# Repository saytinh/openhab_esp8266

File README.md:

# openhab_esp8266
Playground in smart home with openhab and esp8266. This one is built based on:

1. Openhab software (http://www.openhab.org/),  is a software for integrating different home automation systems and technologies into one single solution that allows over-arching automation rules and that offers uniform user interfaces.
2. Mosquitto (http://mosquitto.org/), is an open source (BSD licensed) message broker that implements the MQ Telemetry Transport protocol (MQTT protocol)
3. Adafruit MQTT Library (https://github.com/adafruit/Adafruit_MQTT_Library), is Arduino library used as a MQTT client on esp8266_program
4. Arduino-Temperature-Control-Library (https://github.com/milesburton/Arduino-Temperature-Control-Library), is Arduino Library used for DS18B20 temp sensor on esp8266_program

Thanks all above !!!

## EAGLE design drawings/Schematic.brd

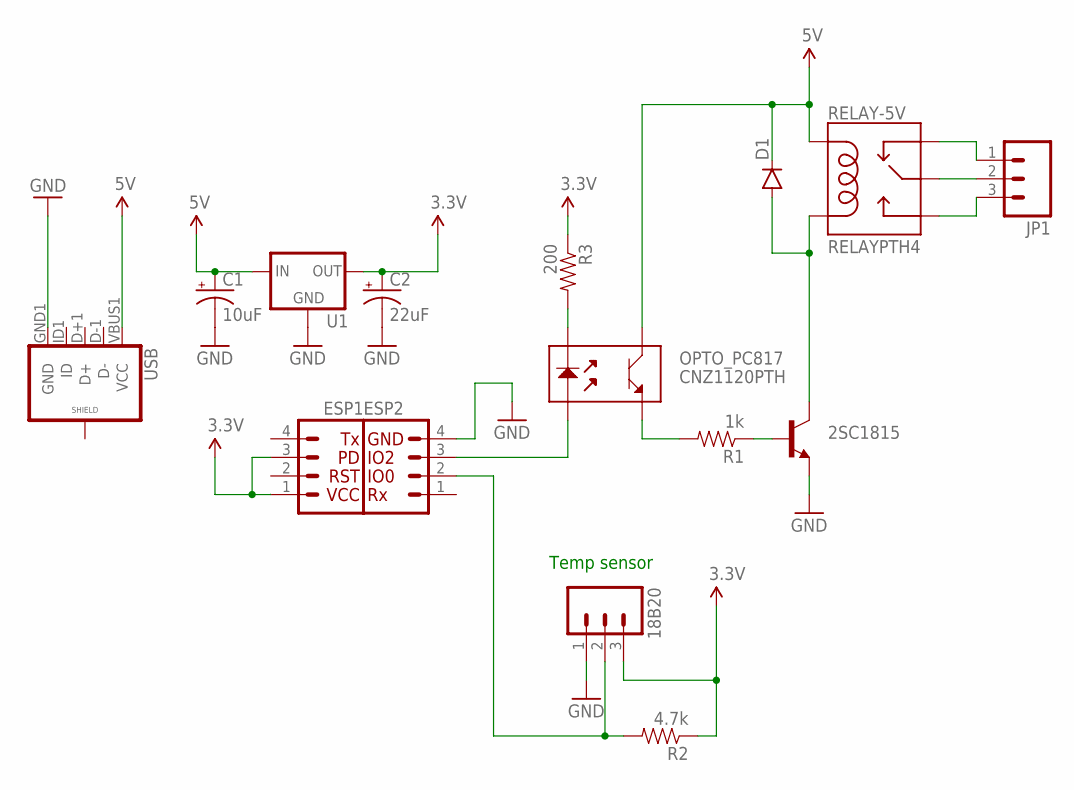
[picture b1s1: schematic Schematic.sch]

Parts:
2SC1815: TRANSISTOR_NPNTO-92-AMMO; TO-92-AMMO
18B20: M03POLAR; MOLEX-1X3
C1: 10uF; CPOL-RADIAL-10UF-25V
C2: 22uF; CPOL-RADIAL-10UF-25V
D1: DIODEPTH; DIODE-1N4001
ESP1: I2C_STANDARD_NO_SILK; 1X04_NO_SILK
ESP2: I2C_STANDARD; 1X04
JP1: M031X03_NO_SILK; 1X03_NO_SILK
OPTO_PC817: CNZ1120PTH; CNZ1120
R1: 1k; AXIAL-0.3
R2: 4.7k; AXIAL-0.3
R3: 200; AXIAL-0.3
RELAY-5V: RELAYPTH4; RELAY-JZC
U1: V_REG_78XXSINK; TO220-IGO
USB: USB_MICROB_PLUGCONN-11752; USB-B-MICRO-SMD_V03

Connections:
3.3V: 18B20.3, C2.1 (+), ESP1.1, ESP1.3, R2.P$1 (1), R3.P$1 (1), U1.GND (OUT)
5V: C1.1 (+), D1.C, OPTO_PC817.4 (3), RELAY-5V.5 (COIL1), U1.OUT (IN), USB.VBUS1 (VCC)
GND: 2SC1815.1 (E), 18B20.1, C1.2 (-), C2.2 (-), ESP2.4, U1.IN (GND), USB.GND1 (GND)
unnamed: OPTO_PC817.3 (4), R1.P$2 (2)
unnamed: 2SC1815.2 (C), D1.A, RELAY-5V.1 (COIL2)
unnamed: 18B20.2, ESP2.2, R2.P$2 (2)
unnamed: ESP2.3, OPTO_PC817.2 (1)
unnamed: OPTO_PC817.1 (2), R3.P$2 (2)
unnamed: JP1.1, RELAY-5V.2 (NC)
unnamed: JP1.3, RELAY-5V.3 (NO)
unnamed: JP1.2, RELAY-5V.4 (MAIN)
unnamed: 2SC1815.3 (B), R1.P$1 (1)

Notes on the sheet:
Temp sensor

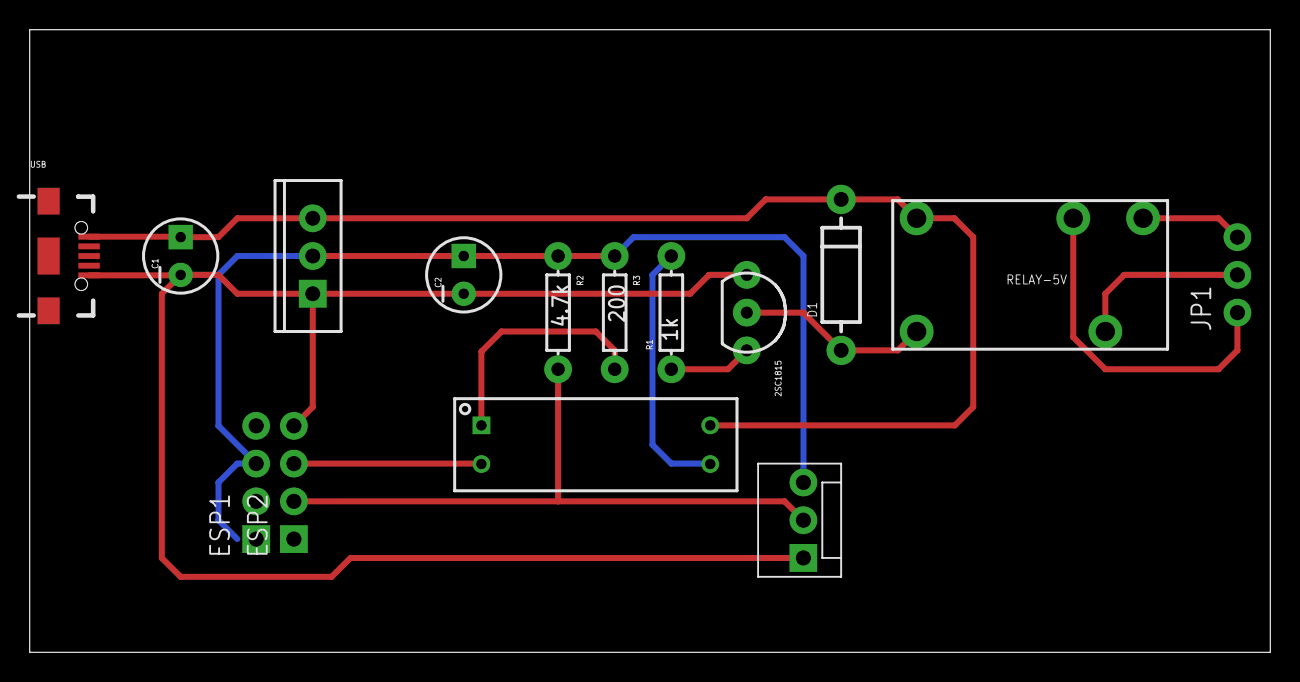
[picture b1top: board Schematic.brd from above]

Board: 2 copper layers, 83.5 x 41.9 mm, 15 parts (0 on the bottom side), 12 nets.

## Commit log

2015-11-07 initial
2015-11-09 revise drawings
2015-11-09 instruction
2015-11-17 remove url

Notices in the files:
parts and their libraries:
SparkFun-Capacitors: Licensing: Creative Commons ShareAlike 4.0 International - https://creativecommons.org/licenses/by-sa/4.0
